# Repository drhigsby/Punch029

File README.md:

# Punch029
 Punch029 Keeb Project

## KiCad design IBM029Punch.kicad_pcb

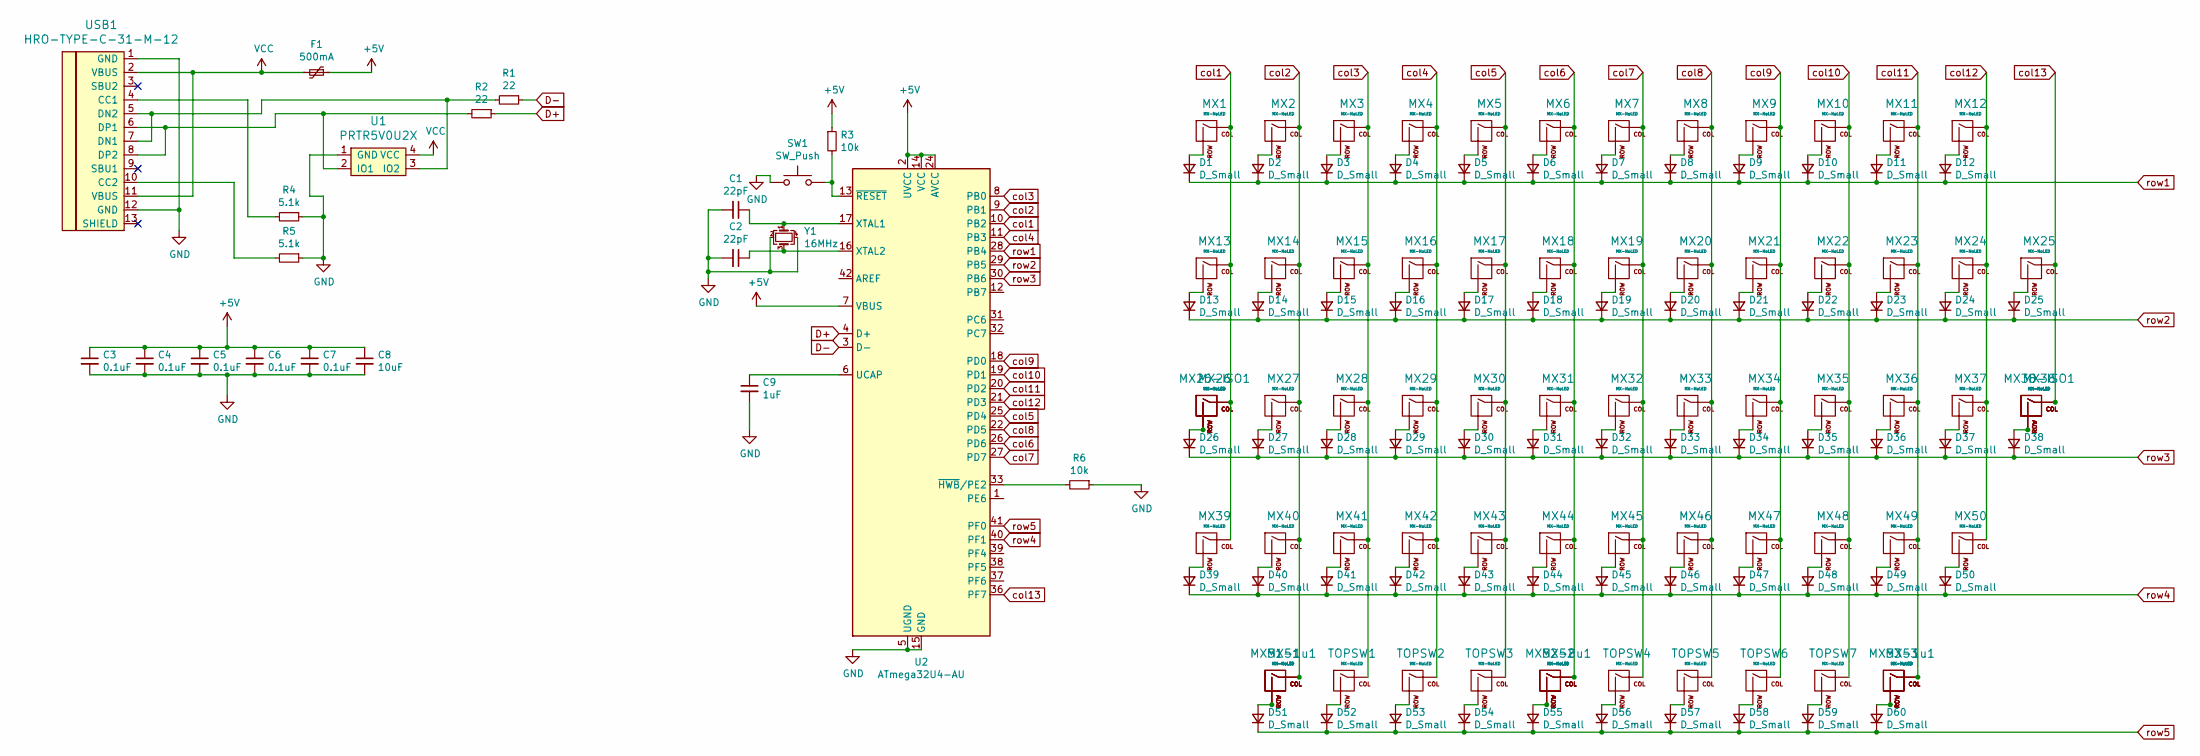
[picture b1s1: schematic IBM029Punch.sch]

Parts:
C1, C2: 22pF; C_0805_2012Metric
C3, C4, C5, C6, C7: 0.1uF; C_0805_2012Metric
C8: 10uF; C_0805_2012Metric
C9: 1uF; C_0805_2012Metric
D1, D2, D3, D4, D5, D6, D7, D8, D9, D10, D11, D12, D13, D14, D15, D16, D17, D18, D19, D20, D21, D22, D23, D24, D25, D26, D27, D28, D29, D30, D31, D32, D33, D34, D35, D36, D37, D38, D39, D40, D41, D42, D43, D44, D45, D46, D47, D48, D49, D50, D51, D52, D53, D54, D55, D56, D57, D58, D59, D60: D_Small; D_SOD-123
F1: 500mA; Fuse_1206_3216Metric
MX1, MX2, MX3, MX4, MX5, MX6, MX7, MX8, MX9, MX10, MX11, MX12, MX14, MX15, MX16, MX17, MX18, MX19, MX20, MX21, MX22, MX23, MX24, MX27, MX28, MX29, MX30, MX31, MX32, MX33, MX34, MX35, MX36, MX37, MX40, MX41, MX42, MX43, MX44, MX45, MX46, MX47, MX48, MX49, MX51-1u1, MX53-1u1: MX-NoLED; MX-1U-NoLED
MX13, MX38: MX-NoLED; MX-1.25U-NoLED
MX25, MX26, MX51, MX53: MX-NoLED; MX-1.5U-NoLED
MX26-ISO1, MX38-ISO1: MX-NoLED; MX-ISO-ReversedStabilizers
MX39: MX-NoLED; MX-2U-ReversedStabilizers-NoLED
MX50: MX-NoLED; MX-1.75U-NoLED
MX52: MX-NoLED; MX-7U-ReversedStabilizers-NoLED
MX52-8u1: MX-NoLED; MX-8U-ReversedStabilizers-NoLED
R1, R2: 22; R_0805_2012Metric
R3, R6: 10k; R_0805_2012Metric
R4, R5: 5.1k; R_0805_2012Metric
SW1: SW_Push; SKQG-1155865
TOPSW1, TOPSW2, TOPSW3, TOPSW4, TOPSW5, TOPSW6, TOPSW7: MX-NoLED; KailhChoc-1U
U1: PRTR5V0U2X; SOT143B
U2: ATmega32U4-AU; TQFP-44_10x10mm_P0.8mm
USB1: HRO-TYPE-C-31-M-12; HRO-TYPE-C-31-M-12-Assembly
Y1: 16MHz; Crystal_SMD_3225-4Pin_3.2x2.5mm

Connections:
+5V: C3.1, C4.1, C5.1, C6.1, C7.1, C8.1, F1.1, R3.1, U2.2 (UVCC), U2.7 (VBUS), U2.14 (VCC), U2.24 (AVCC), U2.34 (VCC), U2.44 (AVCC)
D+: R2.1, U2.4 (D+)
D-: R1.1, U2.3 (D-)
GND: C1.2, C2.2, C3.2, C4.2, C5.2, C6.2, C7.2, C8.2, C9.2, R4.1, R5.1, R6.1, SW1.1, U1.1 (GND), U2.5 (UGND), U2.15 (GND), U2.23 (GND), U2.35 (GND), U2.43 (GND), USB1.1 (GND), USB1.12 (GND), Y1.2, Y1.4
unnamed: C1.1, U2.17 (XTAL1), Y1.1
unnamed: C2.1, U2.16 (XTAL2), Y1.3
unnamed: C9.1, U2.6 (UCAP)
unnamed: D1.2 (A), MX1.2 (ROW)
unnamed: D2.2 (A), MX2.2 (ROW)
unnamed: D3.2 (A), MX3.2 (ROW)
unnamed: D4.2 (A), MX4.2 (ROW)
unnamed: D5.2 (A), MX5.2 (ROW)
unnamed: D6.2 (A), MX6.2 (ROW)
unnamed: D7.2 (A), MX7.2 (ROW)
unnamed: D8.2 (A), MX8.2 (ROW)
unnamed: D9.2 (A), MX9.2 (ROW)
unnamed: D10.2 (A), MX10.2 (ROW)
unnamed: D11.2 (A), MX11.2 (ROW)
unnamed: D12.2 (A), MX12.2 (ROW)
unnamed: D13.2 (A), MX13.2 (ROW)
unnamed: D14.2 (A), MX14.2 (ROW)
unnamed: D15.2 (A), MX15.2 (ROW)
unnamed: D16.2 (A), MX16.2 (ROW)
unnamed: D17.2 (A), MX17.2 (ROW)
unnamed: D18.2 (A), MX18.2 (ROW)
unnamed: D19.2 (A), MX19.2 (ROW)
unnamed: D20.2 (A), MX20.2 (ROW)
unnamed: D21.2 (A), MX21.2 (ROW)
unnamed: D22.2 (A), MX22.2 (ROW)
unnamed: D23.2 (A), MX23.2 (ROW)
unnamed: D24.2 (A), MX24.2 (ROW)
unnamed: D25.2 (A), MX25.2 (ROW)
unnamed: D26.2 (A), MX26.2 (ROW), MX26-ISO1.2 (ROW)
unnamed: D27.2 (A), MX27.2 (ROW)
unnamed: D28.2 (A), MX28.2 (ROW)
unnamed: D29.2 (A), MX29.2 (ROW)
unnamed: D30.2 (A), MX30.2 (ROW)
unnamed: D31.2 (A), MX31.2 (ROW)
unnamed: D32.2 (A), MX32.2 (ROW)
unnamed: D33.2 (A), MX33.2 (ROW)
unnamed: D34.2 (A), MX34.2 (ROW)
unnamed: D35.2 (A), MX35.2 (ROW)
unnamed: D36.2 (A), MX36.2 (ROW)
unnamed: D37.2 (A), MX37.2 (ROW)
unnamed: D38.2 (A), MX38.2 (ROW), MX38-ISO1.2 (ROW)
unnamed: D39.2 (A), MX39.2 (ROW)
unnamed: D40.2 (A), MX40.2 (ROW)
unnamed: D41.2 (A), MX41.2 (ROW)
unnamed: D42.2 (A), MX42.2 (ROW)
unnamed: D43.2 (A), MX43.2 (ROW)
unnamed: D44.2 (A), MX44.2 (ROW)
unnamed: D45.2 (A), MX45.2 (ROW)
unnamed: D46.2 (A), MX46.2 (ROW)
unnamed: D47.2 (A), MX47.2 (ROW)
unnamed: D48.2 (A), MX48.2 (ROW)
unnamed: D49.2 (A), MX49.2 (ROW)
unnamed: D50.2 (A), MX50.2 (ROW)
unnamed: D51.2 (A), MX51.2 (ROW), MX51-1u1.2 (ROW)
unnamed: D52.2 (A), TOPSW1.2 (ROW)
unnamed: D53.2 (A), TOPSW2.2 (ROW)
unnamed: D54.2 (A), TOPSW3.2 (ROW)
unnamed: D55.2 (A), MX52.2 (ROW), MX52-8u1.2 (ROW)
unnamed: D56.2 (A), TOPSW4.2 (ROW)
unnamed: D57.2 (A), TOPSW5.2 (ROW)
unnamed: D58.2 (A), TOPSW6.2 (ROW)
unnamed: D59.2 (A), TOPSW7.2 (ROW)
unnamed: D60.2 (A), MX53.2 (ROW), MX53-1u1.2 (ROW)
unnamed: R1.2, U1.3 (IO2), USB1.5 (DN2), USB1.7 (DN1)
unnamed: R2.2, U1.2 (IO1), USB1.6 (DP1), USB1.8 (DP2)
unnamed: R3.2, SW1.2, U2.13 (~RESET)
unnamed: R4.2, USB1.4 (CC1)
unnamed: R5.2, USB1.10 (CC2)
unnamed: R6.2, U2.33 (~HWB~/PE2)
VCC: F1.2, U1.4 (VCC), USB1.2 (VBUS), USB1.11 (VBUS)
col1: MX1.1 (COL), MX13.1 (COL), MX26.1 (COL), MX26-ISO1.1 (COL), MX39.1 (COL), U2.10 (PB2)
col2: MX2.1 (COL), MX14.1 (COL), MX27.1 (COL), MX40.1 (COL), MX51.1 (COL), MX51-1u1.1 (COL), U2.9 (PB1)
col3: MX3.1 (COL), MX15.1 (COL), MX28.1 (COL), MX41.1 (COL), TOPSW1.1 (COL), U2.8 (PB0)
col4: MX4.1 (COL), MX16.1 (COL), MX29.1 (COL), MX42.1 (COL), TOPSW2.1 (COL), U2.11 (PB3)
col5: MX5.1 (COL), MX17.1 (COL), MX30.1 (COL), MX43.1 (COL), TOPSW3.1 (COL), U2.25 (PD4)
col6: MX6.1 (COL), MX18.1 (COL), MX31.1 (COL), MX44.1 (COL), MX52.1 (COL), MX52-8u1.1 (COL), U2.26 (PD6)
col7: MX7.1 (COL), MX19.1 (COL), MX32.1 (COL), MX45.1 (COL), TOPSW4.1 (COL), U2.27 (PD7)
col8: MX8.1 (COL), MX20.1 (COL), MX33.1 (COL), MX46.1 (COL), TOPSW5.1 (COL), U2.22 (PD5)
col9: MX9.1 (COL), MX21.1 (COL), MX34.1 (COL), MX47.1 (COL), TOPSW6.1 (COL), U2.18 (PD0)
col10: MX10.1 (COL), MX22.1 (COL), MX35.1 (COL), MX48.1 (COL), TOPSW7.1 (COL), U2.19 (PD1)
col11: MX11.1 (COL), MX23.1 (COL), MX36.1 (COL), MX49.1 (COL), MX53.1 (COL), MX53-1u1.1 (COL), U2.20 (PD2)
col12: MX12.1 (COL), MX24.1 (COL), MX37.1 (COL), MX50.1 (COL), U2.21 (PD3)
col13: MX25.1 (COL), MX38.1 (COL), MX38-ISO1.1 (COL), U2.36 (PF7)
row1: D1.1 (K), D2.1 (K), D3.1 (K), D4.1 (K), D5.1 (K), D6.1 (K), D7.1 (K), D8.1 (K), D9.1 (K), D10.1 (K), D11.1 (K), D12.1 (K), U2.28 (PB4)
row2: D13.1 (K), D14.1 (K), D15.1 (K), D16.1 (K), D17.1 (K), D18.1 (K), D19.1 (K), D20.1 (K), D21.1 (K), D22.1 (K), D23.1 (K), D24.1 (K), D25.1 (K), U2.29 (PB5)
row3: D26.1 (K), D27.1 (K), D28.1 (K), D29.1 (K), D30.1 (K), D31.1 (K), D32.1 (K), D33.1 (K), D34.1 (K), D35.1 (K), D36.1 (K), D37.1 (K), D38.1 (K), U2.30 (PB6)
row4: D39.1 (K), D40.1 (K), D41.1 (K), D42.1 (K), D43.1 (K), D44.1 (K), D45.1 (K), D46.1 (K), D47.1 (K), D48.1 (K), D49.1 (K), D50.1 (K), U2.40 (PF1)
row5: D51.1 (K), D52.1 (K), D53.1 (K), D54.1 (K), D55.1 (K), D56.1 (K), D57.1 (K), D58.1 (K), D59.1 (K), D60.1 (K), U2.41 (PF0)

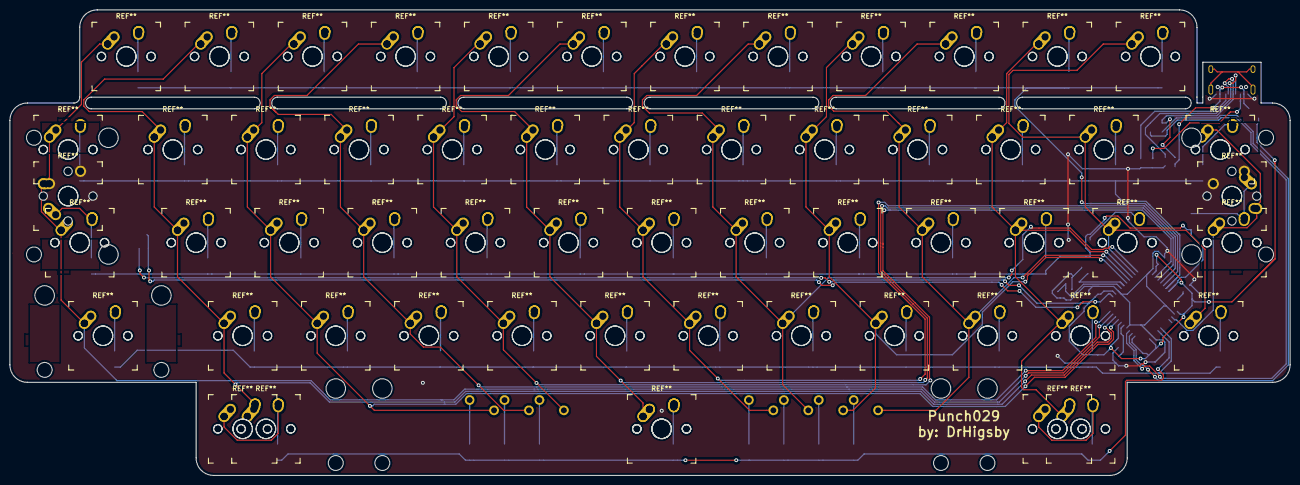
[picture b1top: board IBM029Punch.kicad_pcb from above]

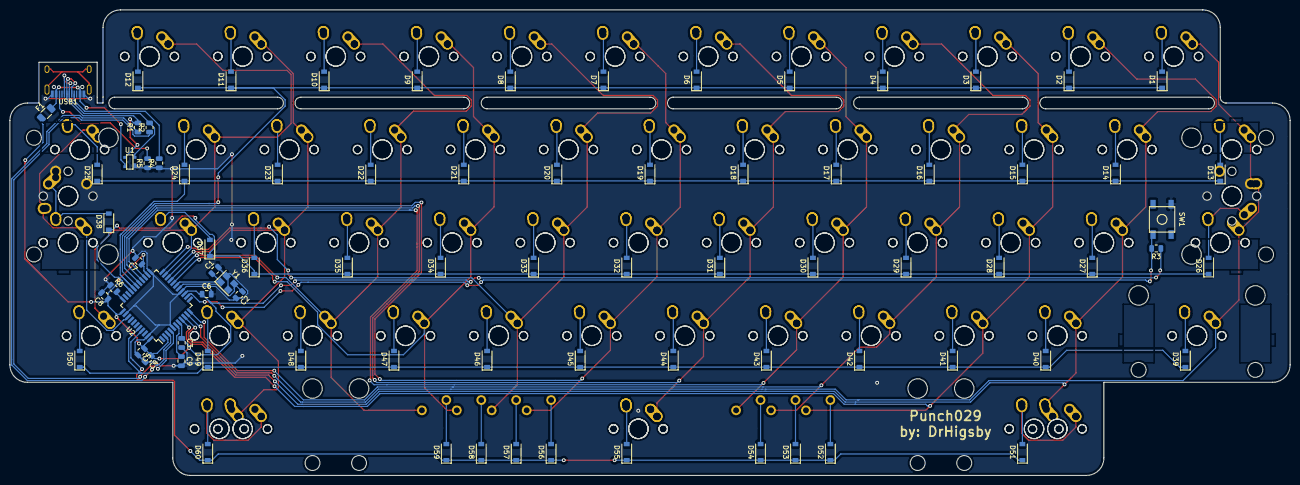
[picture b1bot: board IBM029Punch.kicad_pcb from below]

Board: 2 copper layers, 261.9 x 95.3 mm, 146 parts (81 on the bottom side), 92 nets.

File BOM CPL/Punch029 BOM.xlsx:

Comment | Designator | Footprint | LCSC
22pF | C1,C2 | Capacitor_SMD:C_0805_2012Metric | C1653
0.1uF | C3,C4,C5,C6,C7 | Capacitor_SMD:C_0805_2012Metric | C14663
10uF | C8 | Capacitor_SMD:C_0805_2012Metric | C19702
1uF | C9 | Capacitor_SMD:C_0805_2012Metric | C15849
D_Small | D1,D2,D3,D4,D5,D6,D7,D8,D9,D10,D11,D12,D13,D14,D15,D16,D17,D18,D19,D20,D21,D22,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 | Diode_SMD:D_SOD-123 | C81598
500mA | F1 | Fuse:Fuse_1206_3216Metric | C70076
22.0 | R1,R2 | Resistor_SMD:R_0805_2012Metric | C17561
5.1k | R4,R5 | Resistor_SMD:R_0805_2012Metric | C27834
10k | R3,R6 | Resistor_SMD:R_0805_2012Metric | C17414
SW_Push | SW1 | random-keyboard-parts:SKQG-1155865 | C318884
PRTR5V0U2X | U1 | random-keyboard-parts:SOT143B | C78442
ATmega32U4-AU | U2 | Package_QFP:TQFP-44_10x10mm_P0.8mm | C44854
HRO-TYPE-C-31-M-12 | USB1 | Type-C:HRO-TYPE-C-31-M-12-Assembly | C165948
16MHz | Y1 | Crystal:Crystal_SMD_3225-4Pin_3.2x2.5mm | C13738
